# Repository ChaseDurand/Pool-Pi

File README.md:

#  Pool-Pi

Pool-Pi is a hardware+software system for interfacing with Goldline/Hayward Aqualogic pool control boards over WiFi via a Raspberry Pi. It adds wireless capabilities to non-wireless control boards and a web interface for viewing updates and sending commands.

## Demo Video
This video shows multiple clients interfacing with the unit and demonstrates display updates, button presses, menu controls, blinking display characters, and LED updates.

https://user-images.githubusercontent.com/50851884/149863222-32523871-b4b8-4c59-9fa8-fe185a0315eb.mov

## Overview

Pool-Pi provides a web interface which emulates a local PS-8 display, allowing for the same controls accessible from the physical unit. The serial bus exposes all 14 aux relays regardless of local display, so emulation of a PS-16 display is possible, allowing additional relays to be added without purchasing a larger local interface. An RS485 adapter is used to read and send messages in accordance with the [Aqualogic serial communication protocol](/docs/PROTOCOL_NOTES.md), mimicking an OEM device. The system also adds logging, which is unavailable on the OEM unit. A simplified GUI is available to show the most frequently used commands.

## Setup
Project requirements and instructions can be found in [docs/SETUP.md](/docs/SETUP.md).

## Acknowledgements
Thank you to other people who have put their own resources/solutions for solving this problem online, including [draythomp](http://www.desert-home.com/), [swilson](https://github.com/swilson/aqualogic), and Pete Tompkins.

## Disclaimer
This project is not endorsed or affiliated with Goldline/Hayward in any way.

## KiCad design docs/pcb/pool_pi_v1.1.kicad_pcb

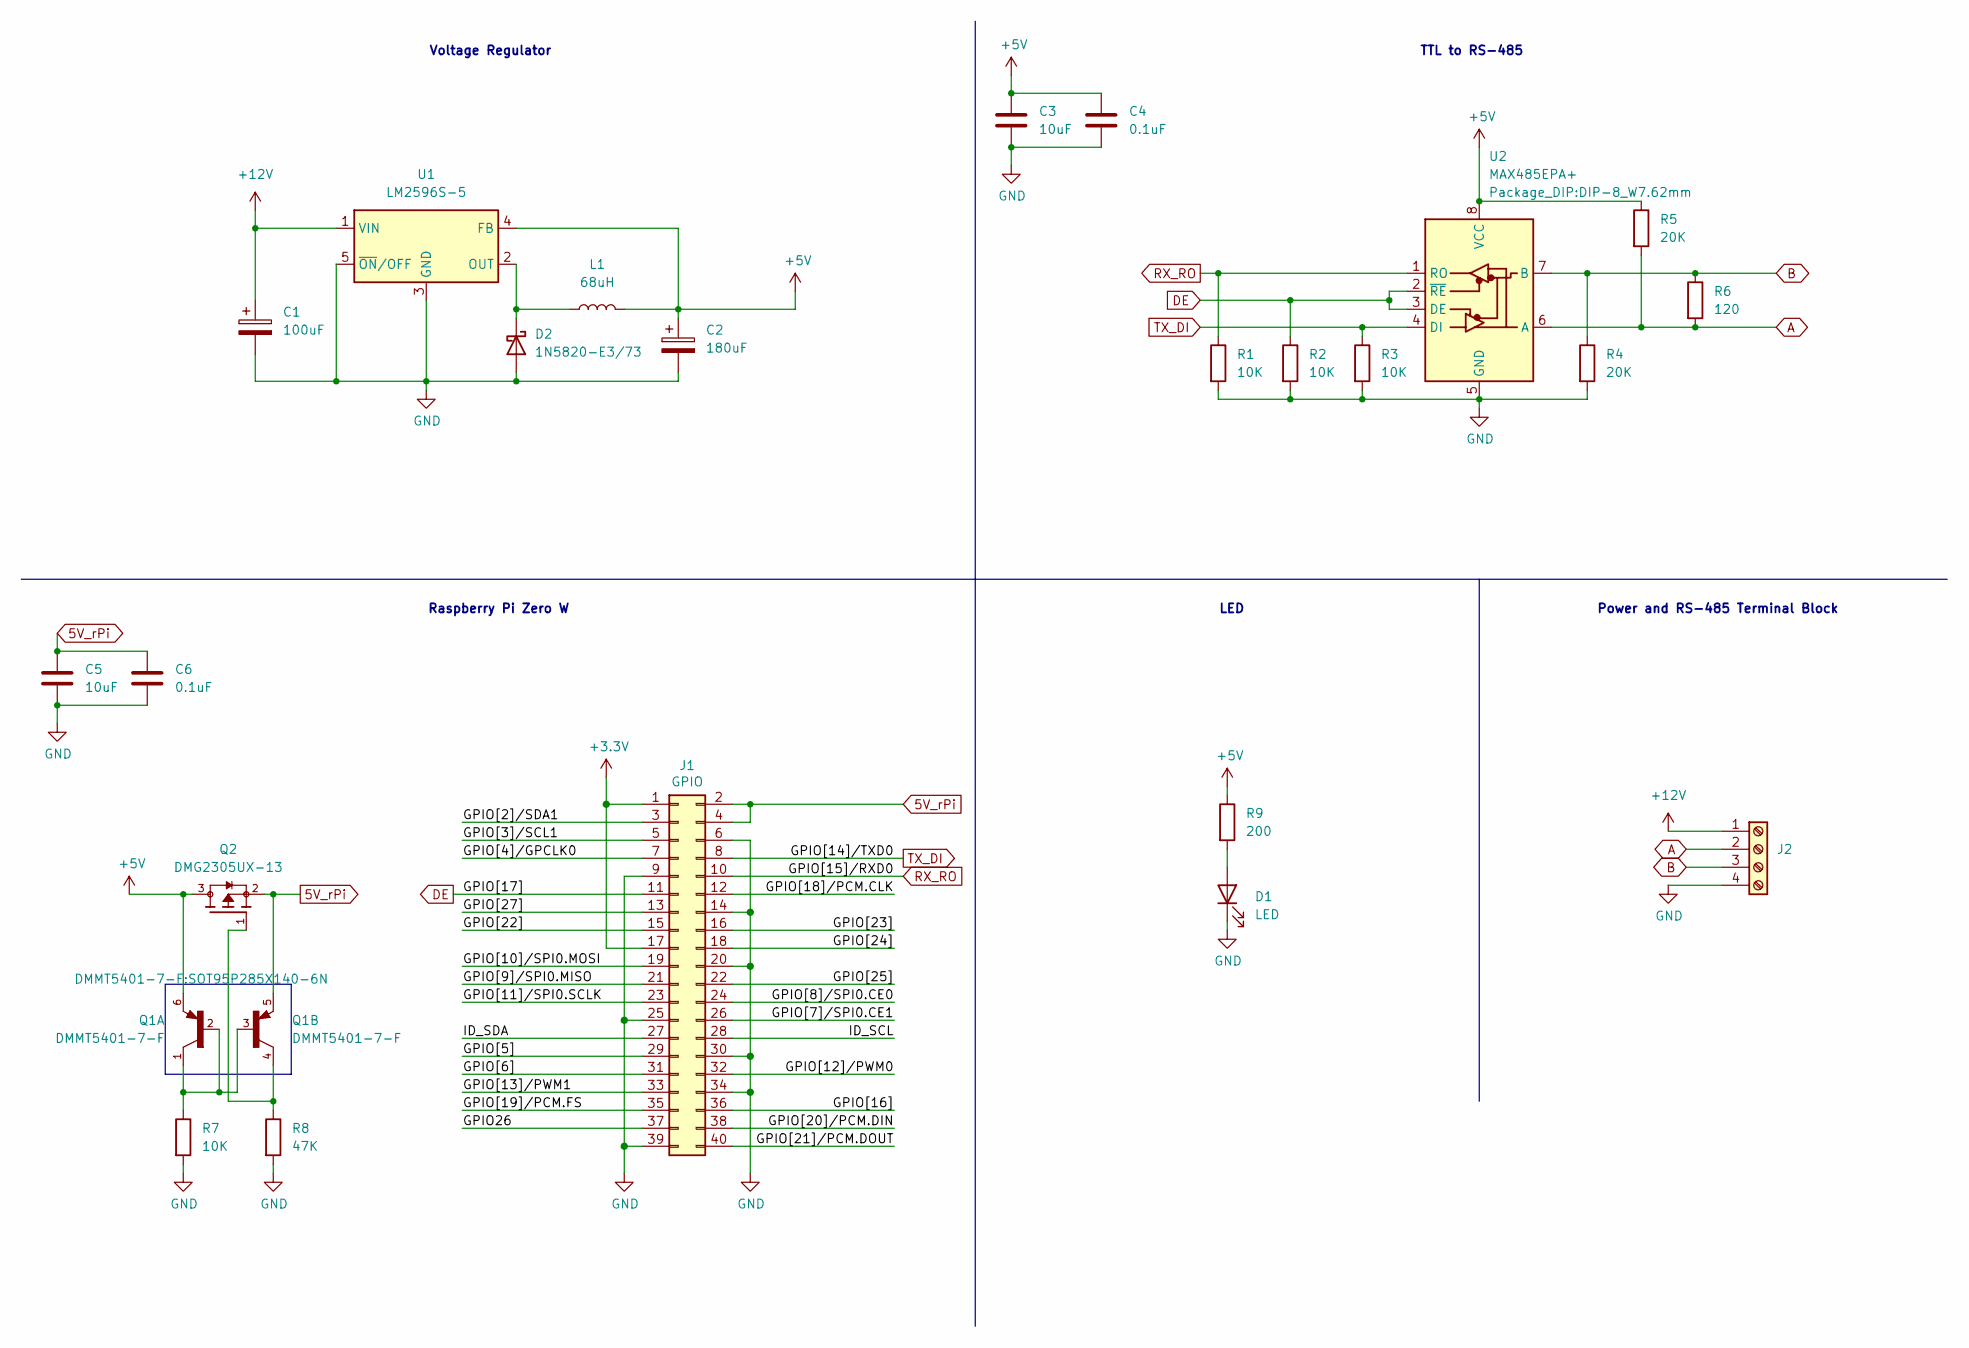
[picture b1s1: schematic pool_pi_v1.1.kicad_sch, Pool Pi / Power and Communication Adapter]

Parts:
C1: 100uF; CP_Radial_D8.0mm_P5.00mm; Part EEU-FR1H101B
C2: 180uF; CP_Radial_D8.0mm_P3.50mm; Part EEU-FR1V181
C3, C5: 10uF; C_0805_2012Metric; Part C0805C106K8PAC
C4, C6: 0.1uF; C_0805_2012Metric; Part C0805C104M5RACTU
D1: LED; LED_D4.0mm; Part C4SMA-GGY-CU2W37A1
D2: 1N5820-E3/73; D_DO-201AD_P12.70mm_Horizontal
J1: GPIO; PinSocket_2x20_P2.54mm_Vertical
J2: 1711042; TerminalBlock_Phoenix_MKDS-1,5-4_1x04_P5.00mm_Horizontal
L1: 68uH; L_12x12mm_H8mm; Part MSS1278H-683KED
Q1: DMMT5401-7-F; SOT95P285X140-6N; PARTREV 8
Q2: DMG2305UX-13; SOT91P240X110-3N; PARTREV 09/2018
R1, R2, R3, R7: 10K; R_Axial_DIN0207_L6.3mm_D2.5mm_P7.62mm_Horizontal; Part CCF0710K0JKE36
R4, R5: 20K; R_Axial_DIN0207_L6.3mm_D2.5mm_P7.62mm_Horizontal; Part CCF0720K0JKE36
R6: 120; R_Axial_DIN0207_L6.3mm_D2.5mm_P7.62mm_Horizontal; Part CCF07120RGKE36
R8: 47K; R_Axial_DIN0207_L6.3mm_D2.5mm_P7.62mm_Horizontal; Part CCF0747K0JKE36
R9: 200; R_Axial_DIN0207_L6.3mm_D2.5mm_P7.62mm_Horizontal; Part CCF07200RGKE36
U1: LM2596S-5; TO-263-5_TabPin3
U2: MAX485EPA+; DIP-8_W7.62mm

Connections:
5V_rPi: C5.1, C6.1, J1.2, J1.4, Q1.5, Q2.2
+3V3: J1.1, J1.17
+5V: C2.1, C3.1, C4.1, L1.2, Q1.6, Q2.3, R5.1, R9.1, U1.4 (FB), U2.8 (VCC)
+12V: C1.1, J2.1, U1.1 (VIN)
/GPIO26: J1.37
/GPIO[2]/SDA1: J1.3
/GPIO[3]/SCL1: J1.5
/GPIO[4]/GPCLK0: J1.7
/GPIO[5]: J1.29
/GPIO[6]: J1.31
/GPIO[7]/SPI0.CE1: J1.26
/GPIO[8]/SPI0.CE0: J1.24
/GPIO[9]/SPI0.MISO: J1.21
/GPIO[10]/SPI0.MOSI: J1.19
/GPIO[11]/SPI0.SCLK: J1.23
/GPIO[12]/PWM0: J1.32
/GPIO[13]/PWM1: J1.33
/GPIO[16]: J1.36
/GPIO[18]/PCM.CLK: J1.12
/GPIO[19]/PCM.FS: J1.35
/GPIO[20]/PCM.DIN: J1.38
/GPIO[21]/PCM.DOUT: J1.40
/GPIO[22]: J1.15
/GPIO[23]: J1.16
/GPIO[24]: J1.18
/GPIO[25]: J1.22
/GPIO[27]: J1.13
/ID_SCL: J1.28
/ID_SDA: J1.27
A: J2.2, R5.2, R6.2, U2.6 (A)
B: J2.3, R4.1, R6.1, U2.7 (B)
DE: J1.11, R2.1, U2.2 (~RE), U2.3 (DE)
GND: C1.2, C2.2, C3.2, C4.2, C5.2, C6.2, D1.1 (K), D2.2 (A), J1.6, J1.9, J1.14, J1.20, J1.25, J1.30, J1.34, J1.39, J2.4, R1.2, R2.2, R3.2, R4.2, R7.2, R8.2, U1.3 (GND), U1.5 (~ON/OFF), U2.5 (GND)
unnamed: D1.2 (A), R9.2
unnamed: D2.1 (K), L1.1, U1.2 (OUT)
unnamed: Q1.1, Q1.2, Q1.3, R7.1
unnamed: Q1.4, Q2.1, R8.1
RX_RO: J1.10, R1.1, U2.1 (RO)
TX_DI: J1.8, R3.1, U2.4 (DI)

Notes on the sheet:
Power and RS-485 Terminal Block
LED
TTL to RS-485
Raspberry Pi Zero W
Voltage Regulator

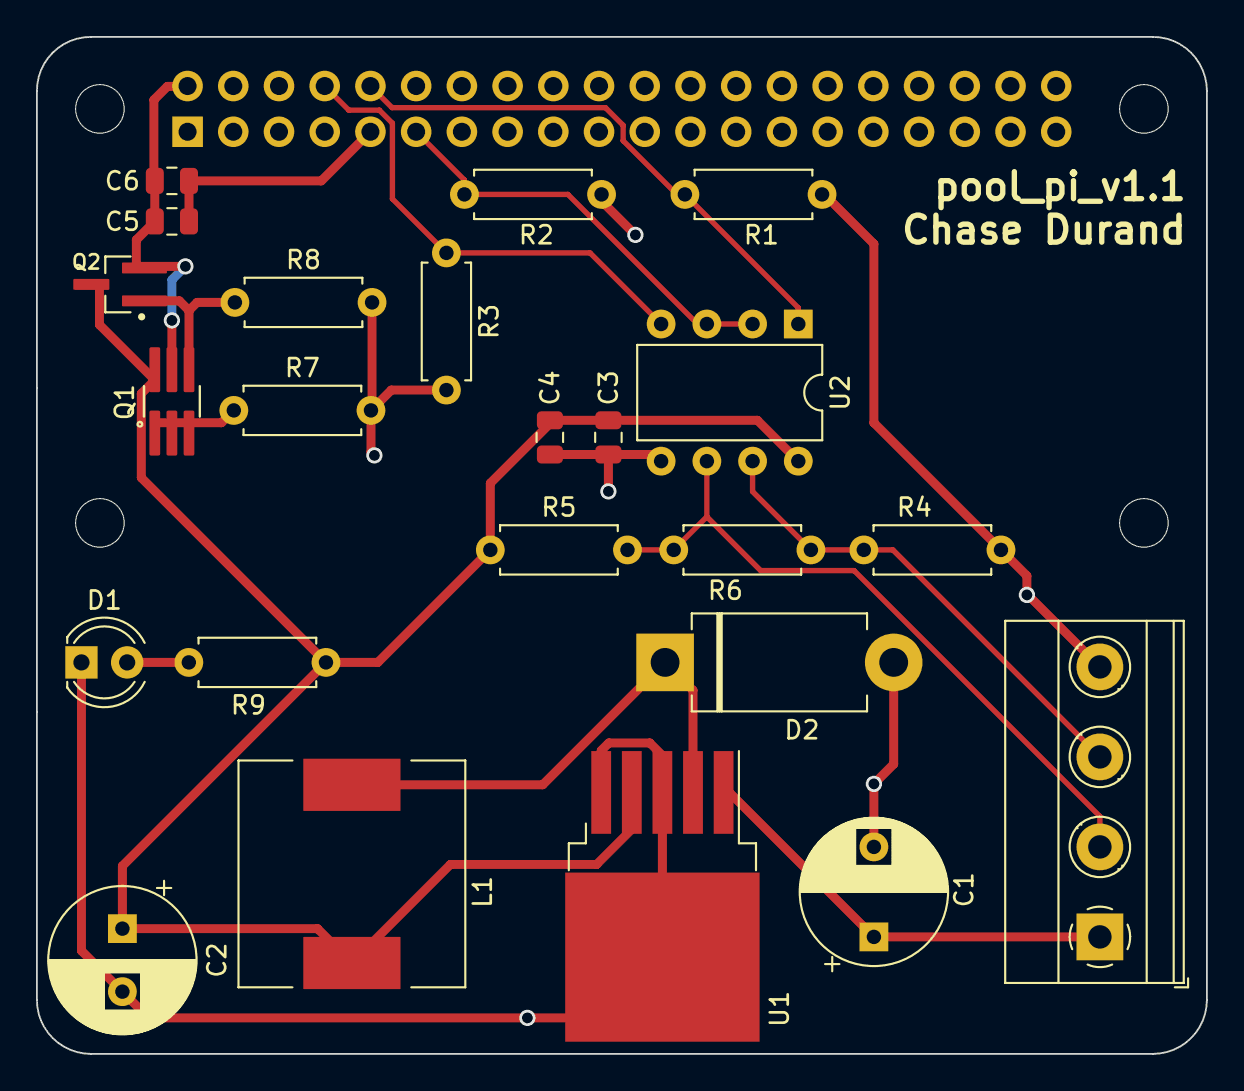
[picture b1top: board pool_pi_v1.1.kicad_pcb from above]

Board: 2 copper layers, 65.0 x 56.5 mm, 28 parts (1 on the bottom side), 14 nets.

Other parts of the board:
MH1, MH2, MH3, MH4: MountingHole_2.7mm_M2.5

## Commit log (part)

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2021-11-30 Added model defaults
2021-11-30 Fixed JSON bug
2021-11-30 Added missing semicolons
2021-11-30 Bypassing toJSON method
2021-11-30 Updated sendModel to only send on changes
2021-11-30 Fixed = == bug
2021-11-30 Converted model from class to dict
2021-11-30 Changed json dumps to dump
2021-11-30 Sending dict instead of json
2021-12-01 Create LICENSE
    Added license file
2021-12-09 Added additional data to front end.
2021-12-09 Added air temp parsing.
2021-12-09 Fixed air temp to include value+units
2021-12-09 Fixing air temp parse
2021-12-09 Air temp fix cont.
2021-12-09 Updated index
2021-12-09 Added parsing for pool temp
2021-12-09 Added datetime parsing. Consolidated day and time fields in model.
2021-12-09 Removed trim() in datetime parsing
2021-12-09 Fixed : decoding in parseDateTime
2021-12-09 Updated index to reflect datetime structure changes.
2021-12-09 Troubleshooting parseDateTime
2021-12-09 Updated salinity parsing
2021-12-09 Fixed salinity parsing for very low salt case
2021-12-09 Updated css
2021-12-09 Testing checkbox functionality
2021-12-09 Working on checkbox
2021-12-10 Working on checkbox submission on change
2021-12-10 Testing checkbox logic simplification
2021-12-10 Added pool to web communication for waterfall
2021-12-10 Fixed waterfall led logic
2021-12-10 Troubleshooting led messages
2021-12-10 Removed unused imports
2021-12-11 Debugging
2021-12-11 Changed checkbox js
2021-12-11 Hardcoded waterfall toggle
2021-12-11 Fixed missing ()
2021-12-11 Updated model on command send to prevent model from overwriting new command
2021-12-12 Fixed model
2021-12-12 Fixed bugs
2021-12-12 Fixed index by creating JS object
2021-12-13 Refactoring. Updated PoolModel. Created SerialHandler class. Updated LED structure. Added attribute states.
2021-12-13 Temporarily removed enums
2021-12-13 Model changes
2021-12-14 Updated front end to accept updated poolModel data
2021-12-14 Fixed bug when calling keys
2021-12-14 Fixed LED bug and added blink detection
2021-12-14 Fixed aux9 LED naming issue
2021-12-14 Fixed CRC bug
2021-12-14 Moved parsing sub functions and constants to separate file.
2021-12-14 Moved flag_data_changed to be part of poolModel
2021-12-14 Added notes. Added color coding on front end for states.
2021-12-14 Fixed out of place }. Fixed =/== swap in text coloring logic.
2021-12-15 Minor front end changed. Minor cleanup. Added sid to broadcast response.
2021-12-15 Swapped checkbox for jquery toggle
2021-12-15 Testing multiple switches
2021-12-15 Fixed output for switches
2021-12-15 Swapped log and toggle order
2021-12-16 Switched checksystem to LED instead of switch/versioned control. Added switches to all parameters. Added switch state from front end.
2021-12-16 Added line breaks. Fixed ID selection when parsing JSON.
2021-12-16 Re-added versioning for switches. Added command validation via versioning.
2021-12-16 Trying file write for thread workaround
2021-12-16 Fixed naming bug
2021-12-16 Added file exists check
2021-12-16 Fixed file write args.
2021-12-16 Reverted thread starts. Expanded getCommand.
2021-12-16 Fixed command string creation
2021-12-16 Updated command forming
2021-12-16 Implemented pickle for saving data
2021-12-16 Debugging version key error
2021-12-16 Debugging front end not getting backend updates
2021-12-16 Uninstalled gevent. Adding in features again to ensure functionality.
2021-12-17 Added writing command to file
2021-12-17 Removed old fopen line
2021-12-27 Added error handling for parseAirTemp
2021-12-27 Added buffer clear if checksum doesn't match instead of attempting to parse message.
2021-12-27 Added function return for checksum mismatch cases.
2021-12-27 Working on web to backend messages
2021-12-27 Fix bool to str in command
2021-12-27 Updated file read+write in getCommand
2021-12-27 Fixed readlines missing ()
2021-12-27 Updated command parsing
2021-12-27 Fixed command version check (str vs int)
2021-12-27 Added second state check for command
2021-12-27 Added switch from true/on and false/off
2021-12-27 Moved true/on false/off to front end
2021-12-28 Added aux4 command
2021-12-28 Fixed send/write name issue
2021-12-29 Moved operations around to reduce delay between message parsing and sending command.
2022-01-01 Added commandHandler and basic command checking logic
2022-01-01 Reduced send time delay
2022-01-01 Added timestamps for LED/model messages and logic for ensuring a new model update has been seen before retrying a command. Adjusted send time delay.
2022-01-02 Removed auxs 7-14. Adjusted web layout.
2022-01-02 Added in aux 7-14 (need to filter on LED parse)
2022-01-02 Changed togglerOff back to toggler off
2022-01-03 Removed unused message+broadcast form and event.
2022-01-03 Fixed non-updated class name
2022-01-03 Fixed old class name
2022-01-03 Updated labels to match physical panel.
2022-01-03 Fixed css and valve names.
2022-01-03 Updated background
2022-01-03 Split display into 2 lines
2022-01-03 Updated css. Fixed json parsing.
2022-01-03 Fixed css naming bug
2022-01-03 Updated css for text display
2022-01-03 Fixed sizing bug for last row of switches
2022-01-03 Added panel css
2022-01-03 Added hover effect for switches
2022-01-04 Updated command sending order of operations to prioritize keep alive response
2022-01-04 Fixed typo and added additional check for checkCommand.
2022-01-04 Removed time delay for command attempts
2022-01-05 Greatly improved command response. Removed unused web functions.
2022-01-05 Updated gif placement
2022-01-05 Began adding other commands.
2022-01-05 Fixed class/object name issue
2022-01-06 Added outbound command forming (aux4 only)
2022-01-06 Added additional commands
2022-01-06 Added parts list
2022-01-06 Added protocol notes
2022-01-06 Moved countKA out of global scope to commandHandler.keepAliveCount
2022-01-06 Corrected light command
2022-01-06 Corrected lights command
2022-01-06 Added images to readme
2022-01-07 Restructured repo
2022-01-07 Updated image and doc links
2022-01-07 Moved parts of readme to setup
2022-01-07 Added test button
2022-01-07 Added second button and css
2022-01-07 Fixed jquery selector error
2022-01-07 Added additional buttons
2022-01-07 Updated front end
2022-01-08 Updated front end.
2022-01-08 Updated front end. Updated gui image.
2022-01-08 Cleaned up code. Added additional comments.
2022-01-08 Updated troubleshooting guide
2022-01-09 Added additional check in getCommand
2022-01-09 Renamed web events. Added favicon. Modified path references.'
2022-01-09 Updated model
2022-01-09 Stripped attributes not needed on front end before transmitting.
2022-01-09 Fixed json bug from missing copy()
2022-01-09 Updated getCommand to explicitly read only one line.
2022-01-09 Updated frame forming to add x00 after x10
2022-01-10 Cleaned up comments
2022-01-10 Changed favicon from svg to ico
2022-01-10 Added config.txt
2022-01-10 Removed erroneous import
2022-01-10 Changed na to 0 to prevent int error when parsing on back end
2022-01-10 Updated display parsing to update changed flag even if error occurs
2022-01-11 Added color output for checksum mismatch.
2022-01-11 Added extra dle stx/etx checks for invalid message
2022-01-11 Added checksum error printing
2022-01-11 Reordered checksum and DLESTX/ETX checks
2022-01-12 Fixed logic error for overlay.
2022-01-12 Added overlay on switch toggle
2022-01-12 Added additional flag data changed on command success.
2022-01-12 Added basic button effect, broke panel css
2022-01-13 Modified console log output
2022-01-13 Updated display parsing.
2022-01-13 Updated display parsing. Decoded to utf8 on front end.
2022-01-13 Updated display parsing structure
2022-01-13 Bug fixes
2022-01-13 Changed display to string
2022-01-13 Updated display parsing message.
2022-01-13 Fixed mask bug
2022-01-13 Fixed mask logic bug
2022-01-13 Added blinking to front end
2022-01-13 Added favicon/logo to title
2022-01-14 Tweaked parsing
2022-01-14 Overhauled front end. Swapped toggles to buttons. Added blinking leds. Added check system LED.
2022-01-14 Bug fixes.
2022-01-14 More bug fixes.
2022-01-14 Bugs
2022-01-14 Fixed screen blinking
2022-01-14 Corrected command confirm
2022-01-14 Corrected command messaging.
2022-01-14 Fixed other button state check
2022-01-14 Cleared command queue on startup
2022-01-14 Updated gui image
2022-01-14 Removed unused commands
2022-01-15 Removed unused css
2022-01-15 Updated updateParameter to fix checkSystem LED
2022-01-15 Added simple web page
2022-01-15 Renamed simple function
2022-01-15 Updated simple front end
2022-01-15 Updated notes
2022-01-15 Cleaned up formatting.
2022-01-15 Updated sending_message flag name
2022-01-15 Slight clean up
2022-01-15 Consolidated commands to commands.py
2022-01-16 Moved superchlorinate and systemoff from buttons to states.
2022-01-17 Updated protocol notes to include configuration menu
2022-01-17 Added simple-websocket
2022-01-17 Updated setup
2022-01-17 Clarification
2022-01-17 Added setup image
2022-01-17 Added raspberry pi setup tutorial link
2022-01-17 Implemeneted demo timeout notification
2022-01-17 Added clearTimeout
2022-01-17 Updated disconnect timeout feedback to user
2022-01-17 Updated timeout message. Removed console logs
2022-01-17 Fixed timeout message.
2022-01-17 Added initial display message to front end
2022-01-17 Removed completed todos
2022-01-17 Updated setup documentation and added additional images.
2022-01-17 Updated documentation
2022-01-17 Updated docs
2022-01-17 Updated to ignore log file
2022-01-17 Added additional logging
2022-01-17 Updated logging and fixed bug in parseLED logging
2022-01-17 Cleaned up comments and printing
2022-01-18 Moved command log from serialHandler send to pool-pi
2022-01-18 Testing rotating log files
2022-01-18 Updated logging to use root logger
2022-01-18 Changed logging interval to daily (midnight)
2022-01-18 Updated formatting
2022-01-18 Added url preview image
2022-01-18 Added video demo
2022-01-18 Removed video demo from repo (will add directly on github)
2022-01-18 Added demo video
2022-01-18 Removed large demo video file
2022-01-18 Removed colorama
2022-01-18 Fixed cropping on gui2
2022-01-18 Added todo
2022-01-19 Added automatic startup files and documentation
2022-01-19 Updated execute permissions for setup.sh
2022-01-20 Added notes about exposing all 14 aux parameters
2022-01-26 Added checks for service mode display updates.
2022-01-26 Changed service mode update to logging only.
2022-02-13 Updated wire details in parts list
2022-02-13 Updated protocol notes language
2022-04-19 Fixed ios icon.
2022-05-13 Updated wiring_2 diagram. Added Fritzing file.
2022-05-13 Added overview diagram.
2022-05-23 Removed jquery for vanilla js. Removed old on screen text log.
2022-05-23 Removed jquery source.
2022-05-23 Corrected selection and add event listener loop for menu buttons. Removed unused on connect function.
2022-06-20 Added cursor change to pointer when mouse hovers over buttons.
2022-12-27 Updated SETUP.md doc to reflect no reboot in setup.sh.
2023-01-06 Added 1k pull down to DE to prevent DE from being pulled to 5V during pi startup. Updated parts list, setup, and wiring image.
2023-01-26 Minor refactoring. Removed unused parsing functions. Cleaned up comments, function names, and variable names.
2023-02-04 Moved next state logic from front end to back end. Changed state version from per command to single version for entire model. Some cleanup and renamed variables.
2023-02-04 Clarified protocol notes
2023-02-04 Fixed json name mismatch between front and back end for version.
2023-02-04 Fixed int to str error.
2023-02-04 Fixed pool/spa/spillover next state logic.
2023-02-04 Fixed pool-spa-spillover from falsely throwing error
2023-02-04 Fixed pool/spa/spill bug
2023-05-23 Remove hardcoded paths from setup
2023-06-10 Changed python package from serial (wrong) to pyserial (still imported as serial in py files).
2023-11-19 Added redis and eventlet.
2023-11-19 Fixed spelling mixtake
2023-11-19 Fixed error in venv activation.
2023-11-19 Using socketio from cdn instead of offline.
2023-11-23 Updated setup, req, serial port, and redis parsing.
2023-11-24 Removed eventlet
2023-11-24 Removed print statement for debugging.
2023-11-24 Switched socket.io to v4.6.0
2023-11-24 Removed unnecessary root use in setup.
2023-11-27 Started glx web GUI.
2023-11-27 Removed username pi in path in setup
2024-12-28 Corrected setup script. Added allow_unsafe_werkzeug.
